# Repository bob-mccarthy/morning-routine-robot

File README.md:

# morning-routine-robot
Alarm clock that forces me to do my morning routine

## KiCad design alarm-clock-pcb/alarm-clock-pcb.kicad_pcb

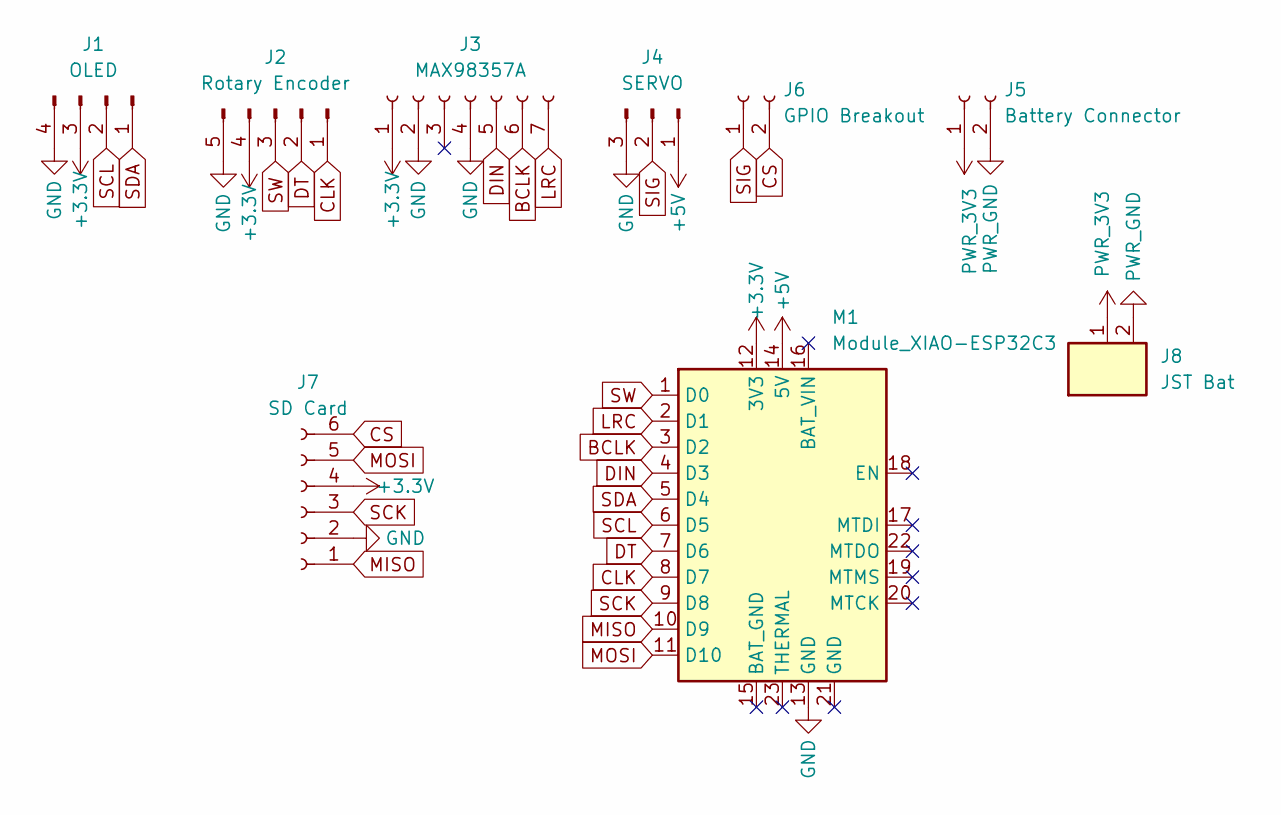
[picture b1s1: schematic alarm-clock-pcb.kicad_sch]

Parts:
J1: OLED; PinHeader_1x04_P2.54mm_Vertical
J2: Rotary Encoder; PinSocket_1x05_P2.54mm_Vertical
J3: MAX98357A; PinSocket_1x07_P2.54mm_Vertical
J4: SERVO; PinHeader_1x03_P2.54mm_Vertical
J5: Battery Connector; PinSocket_1x02_P2.54mm_Vertical
J6: GPIO Breakout; PinSocket_1x02_P2.54mm_Vertical
J7: SD Card; PinSocket_1x06_P2.54mm_Vertical
J8: JST Bat; Header_JST_PH_1x02_P2mm_Vertical_SMD
M1: Module_XIAO-ESP32C3; SeeedStudio_XIAO_ESP32C3

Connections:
+3.3V: J1.3, J2.4, J3.1, J7.4, M1.12 (3V3)
+5V: J4.1, M1.14 (5V)
BCLK: J3.6, M1.3 (D2)
CLK: J2.1, M1.8 (D7)
CS: J6.2, J7.6
DIN: J3.5, M1.4 (D3)
DT: J2.2, M1.7 (D6)
GND: J1.4, J2.5, J3.2, J3.4, J4.3, J7.2, M1.13 (GND)
LRC: J3.7, M1.2 (D1)
MISO: J7.1, M1.10 (D9)
MOSI: J7.5, M1.11 (D10)
PWR_3V3: J5.1, J8.1
PWR_GND: J5.2, J8.2
SCK: J7.3, M1.9 (D8)
SCL: J1.2, M1.6 (D5)
SDA: J1.1, M1.5 (D4)
SIG: J4.2, J6.1
SW: J2.3, M1.1 (D0)

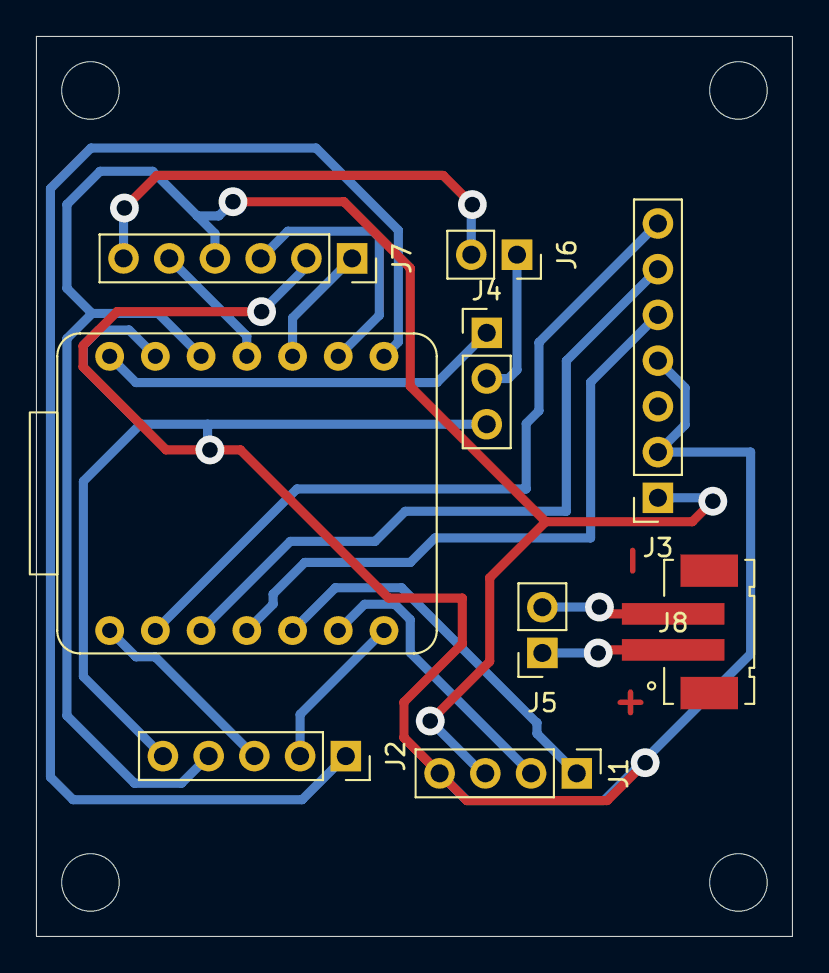
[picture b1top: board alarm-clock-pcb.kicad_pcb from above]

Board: 2 copper layers, 42.0 x 50.0 mm, 9 parts (0 on the bottom side), 18 nets.

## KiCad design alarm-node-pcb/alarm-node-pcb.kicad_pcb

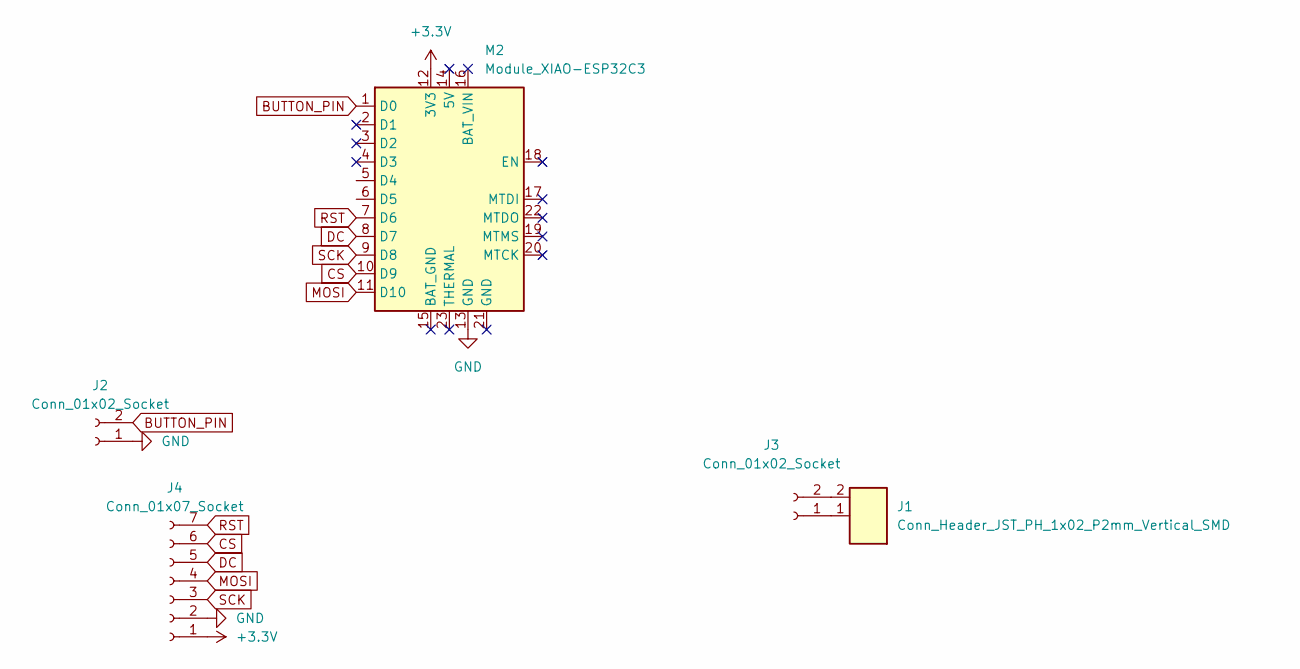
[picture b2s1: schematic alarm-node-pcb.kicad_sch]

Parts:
J1: Conn_Header_JST_PH_1x02_P2mm_Vertical_SMD; Header_JST_PH_1x02_P2mm_Vertical_SMD
J2, J3: Conn_01x02_Socket; PinSocket_1x02_P2.54mm_Vertical
J4: Conn_01x07_Socket; PinSocket_1x07_P2.54mm_Vertical
M2: Module_XIAO-ESP32C3; SeeedStudio_XIAO_ESP32C3

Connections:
+3.3V: J4.1, M2.12 (3V3)
BUTTON_PIN: J2.2, M2.1 (D0)
CS: J4.6, M2.10 (D9)
DC: J4.5, M2.8 (D7)
GND: J2.1, J4.2, M2.13 (GND)
MOSI: J4.4, M2.11 (D10)
unnamed: J1.1, J3.1
unnamed: J1.2, J3.2
RST: J4.7, M2.7 (D6)
SCK: J4.3, M2.9 (D8)

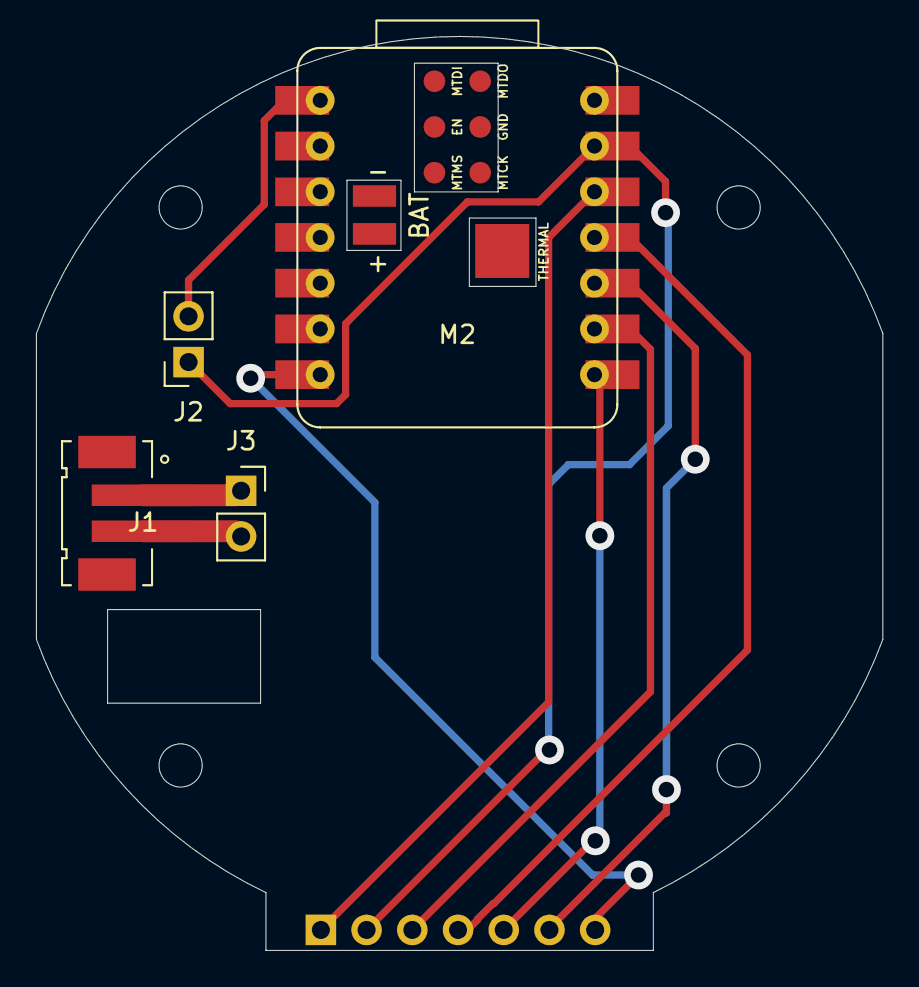
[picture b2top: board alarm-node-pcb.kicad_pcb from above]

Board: 2 copper layers, 47.0 x 50.8 mm, 5 parts (1 on the bottom side), 10 nets.

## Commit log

2024-01-05 home screen + working time
2025-09-02 init repo
2025-09-04 UI Test for the alarm clock server
2025-09-05 basics of alarm node UI done
